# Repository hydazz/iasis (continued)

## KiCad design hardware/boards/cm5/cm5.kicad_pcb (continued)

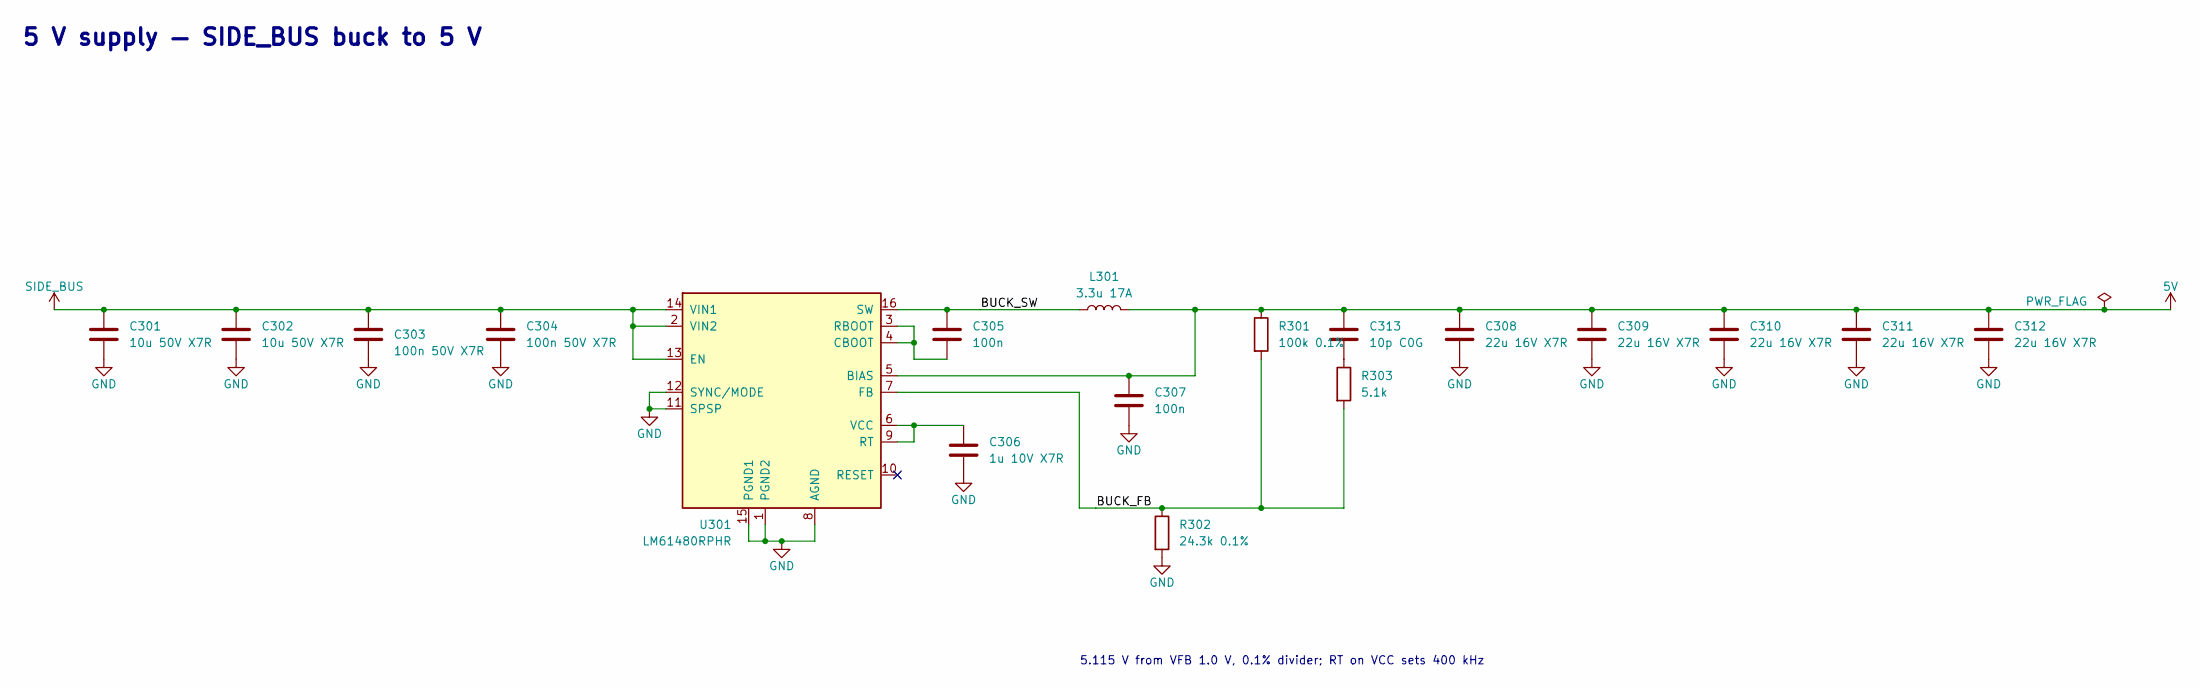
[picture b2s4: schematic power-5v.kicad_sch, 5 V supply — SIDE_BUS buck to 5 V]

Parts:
C301, C302: 10u 50V X7R; C_1210_3225Metric; MPN CL32B106KBJNNNE; LCSC C138687
C303, C304: 100n 50V X7R; C_0402_1005Metric; MPN CL05B104KB54PNC; LCSC C307331
C305, C307: 100n; C_0402_1005Metric; MPN CL05B104KO5NNNC; LCSC C1525
C306: 1u 10V X7R; C_0603_1608Metric; MPN CGA0603X7R105K100JT; LCSC C22399625
C308, C309, C310, C311, C312: 22u 16V X7R; C_1210_3225Metric; MPN CL32B226KOJNNNE; LCSC C55530
C313: 10p C0G; C_0402_1005Metric; MPN CL05C100JB5NNNC; LCSC C32949
L301: 3.3u 17A; L_PROD_PSPMAA0805; MPN PSPMAA0805-3R3M-ANP; LCSC C2962881
R301: 100k 0.1%; R_0402_1005Metric; MPN ARG02BTC1003; LCSC C2984406
R302: 24.3k 0.1%; R_0402_1005Metric; MPN ARG02BTC2432; LCSC C2681592
R303: 5.1k; R_0402_1005Metric; MPN 0402WGF5101TCE; LCSC C25905
U301: LM61480RPHR; TI_RPH0016A; MPN LM61480RPHR; LCSC C3198089

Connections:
5V: C307.1, C308.1, C309.1, C310.1, C311.1, C312.1, C313.1, L301.2, R301.1, U301.5 (BIAS); also elsewhere on the board
/5 V supply/BUCK_FB: R301.2, R302.1, R303.2, U301.7 (FB)
/5 V supply/BUCK_SW: C305.1, L301.1, U301.16 (SW)
GND: C301.2, C302.2, C303.2, C304.2, C306.2, C307.2, C308.2, C309.2, C310.2, C311.2, C312.2, R302.2, U301.1 (PGND2), U301.8 (AGND), U301.11 (SPSP), U301.12 (SYNC/MODE), U301.15 (PGND1); also elsewhere on the board
unnamed: C313.2, R303.1
unnamed: C305.2, U301.3 (RBOOT), U301.4 (CBOOT)
unnamed: C306.1, U301.6 (VCC), U301.9 (RT)
SIDE_BUS: C301.1, C302.1, C303.1, C304.1, U301.2 (VIN2), U301.13 (EN), U301.14 (VIN1); also elsewhere on the board

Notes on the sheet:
5 V supply — SIDE_BUS buck to 5 V
5.115 V from VFB 1.0 V, 0.1% divider; RT on VCC sets 400 kHz

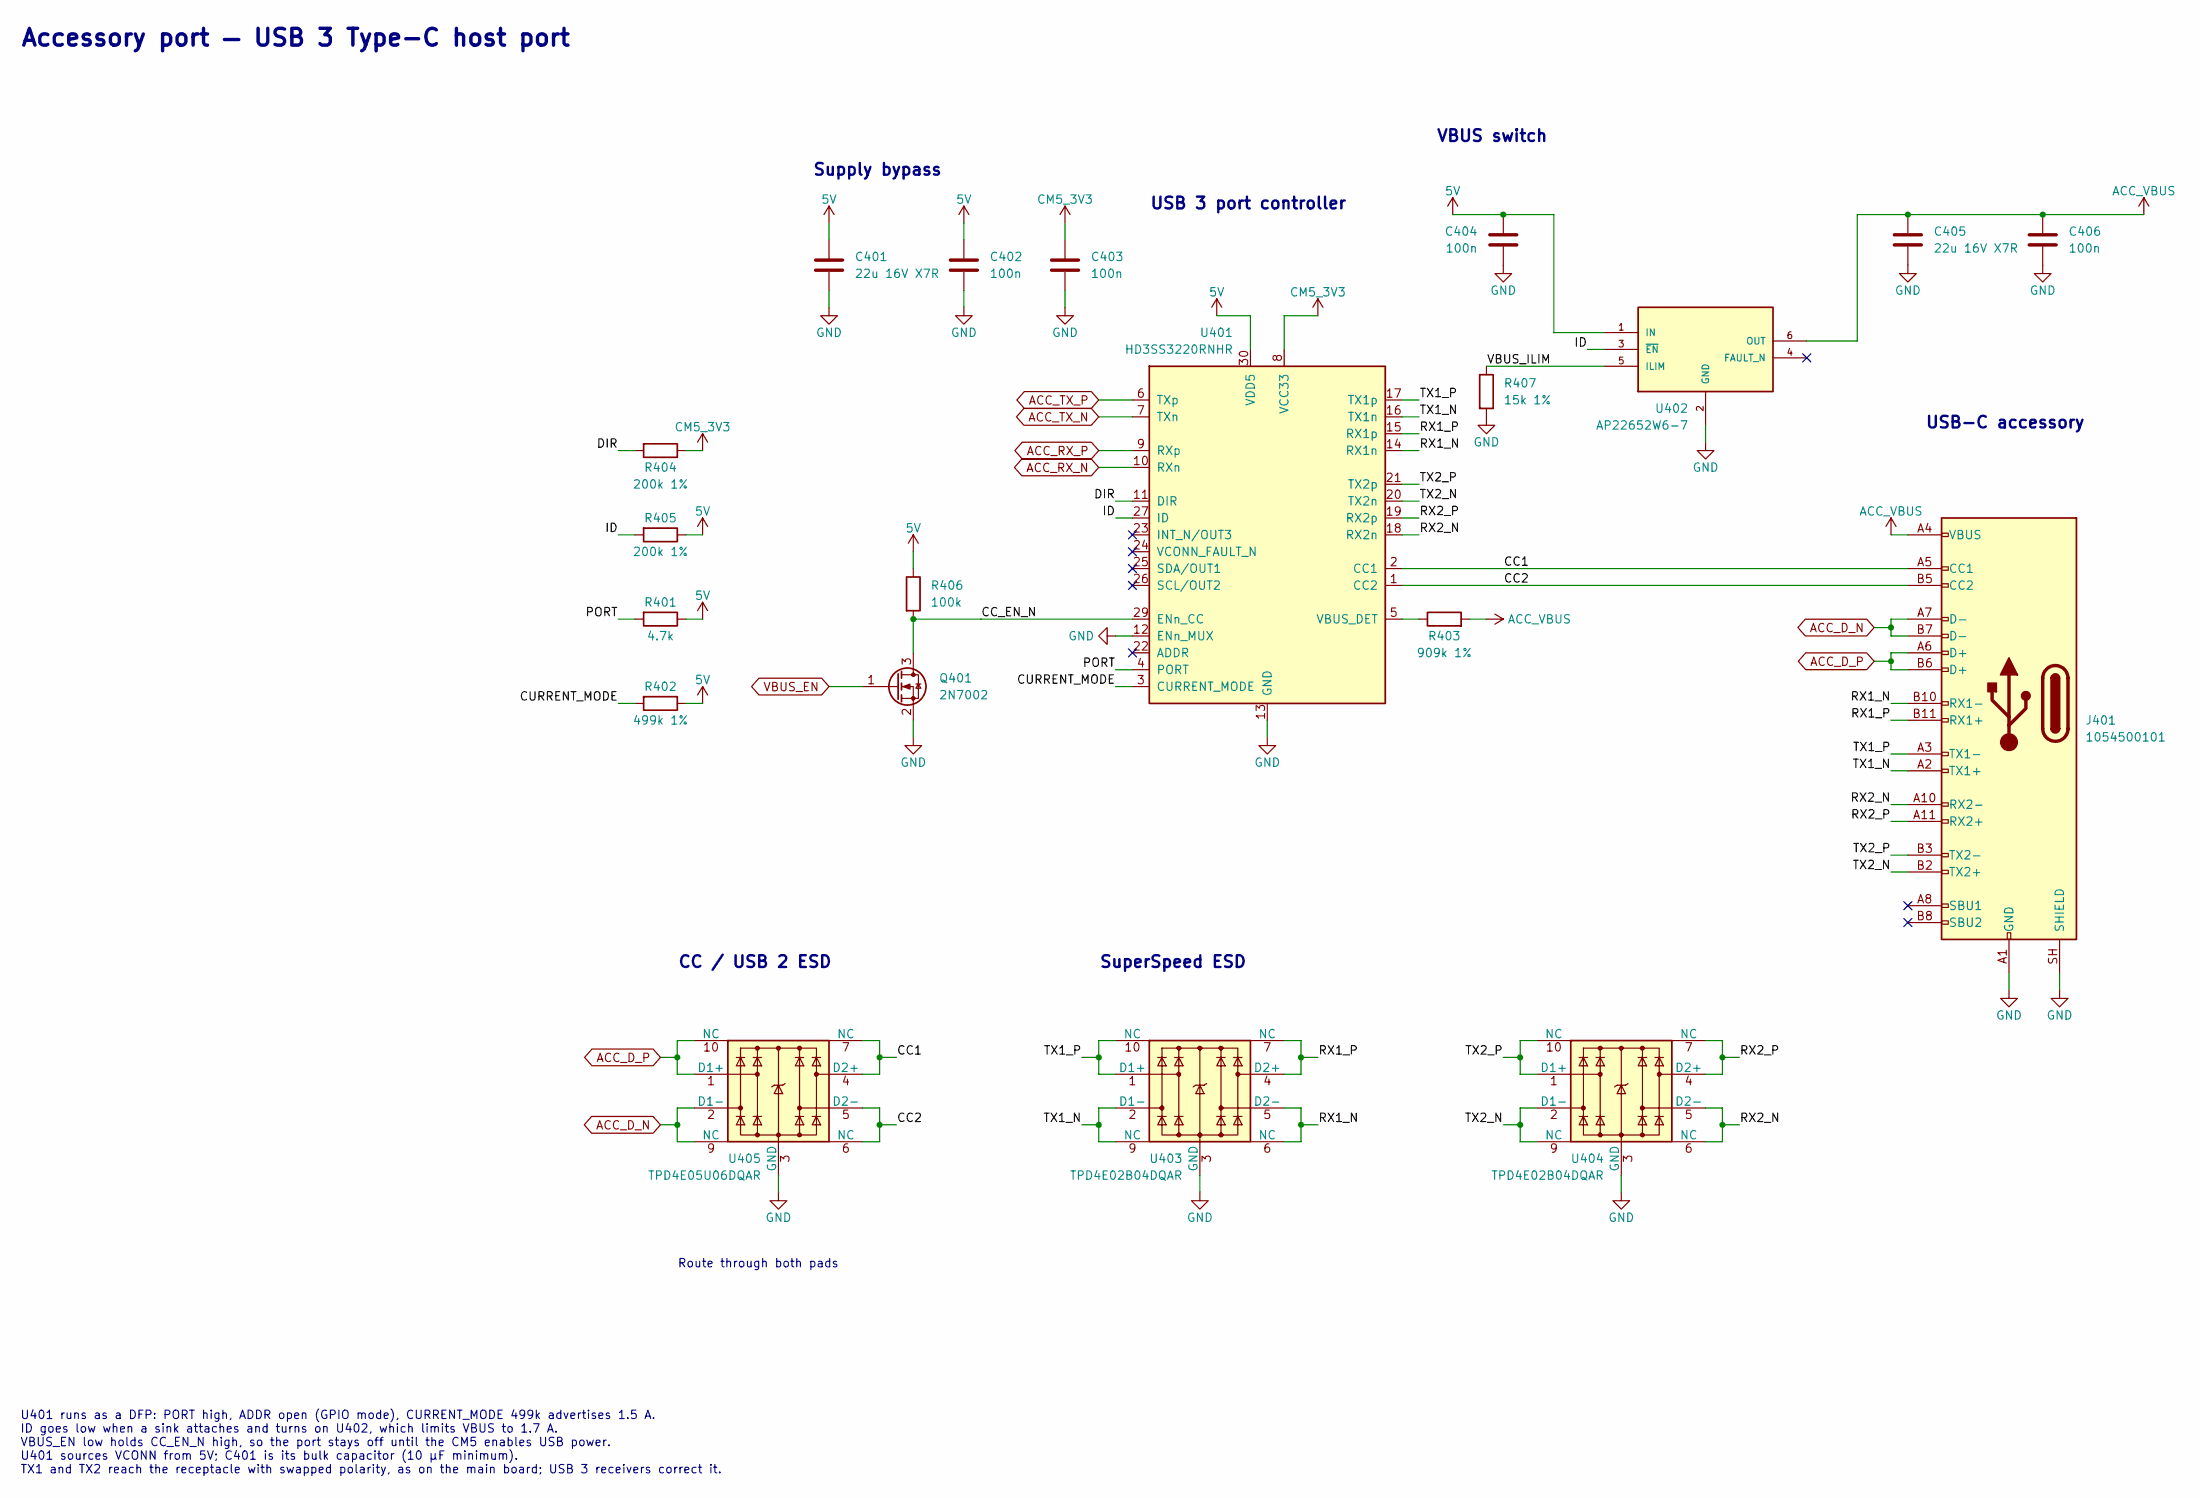
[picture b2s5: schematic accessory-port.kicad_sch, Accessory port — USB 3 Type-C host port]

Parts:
C401, C405: 22u 16V X7R; C_1210_3225Metric; MPN CL32B226KOJNNNE; LCSC C55530
C402, C403, C404, C406: 100n; C_0402_1005Metric; MPN CL05B104KO5NNNC; LCSC C1525
J401: 1054500101; USB_C_Receptacle_Molex_105450-0101; MPN 1054500101; LCSC C134092
Q401: 2N7002; SOT-23; MPN 2N7002; LCSC C8545
R401: 4.7k; R_0402_1005Metric; MPN 0402WGF4701TCE; LCSC C25900
R402: 499k 1%; R_0402_1005Metric; MPN 0402WGF4993TCE; LCSC C25793
R403: 909k 1%; R_0402_1005Metric; MPN 0402WGF9093TCE; LCSC C25799
R404, R405: 200k 1%; R_0402_1005Metric; MPN 0402WGF2003TCE; LCSC C25764
R406: 100k; R_0402_1005Metric; MPN 0402WGF1003TCE; LCSC C25741
R407: 15k 1%; R_0402_1005Metric; MPN 0402WGF1502TCE; LCSC C25756
U401: HD3SS3220RNHR; Texas_RNH0030A_WQFN-30-1EP_2.5x4.5mm_P0.4mm_EP1.2x3.2mm; MPN HD3SS3220RNHR; LCSC C165155
U402: AP22652W6-7; SOT-23-6; MPN AP22652W6-7; LCSC C2158038
U403, U404: TPD4E02B04DQAR; USON-10_2.5x1.0mm_P0.5mm; MPN TPD4E02B04DQAR; LCSC C106794
U405: TPD4E05U06DQAR; USON-10_2.5x1.0mm_P0.5mm; MPN TPD4E05U06DQAR; LCSC C138714

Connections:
5V: C401.1, C402.1, C404.1, R401.1, R402.1, R405.1, R406.1, U401.30 (VDD5), U402.1 (IN); also elsewhere on the board
/Accessory port/CC1: J401.A5 (CC1), U401.2 (CC1), U405.4 (D2+), U405.7 (NC)
/Accessory port/CC2: J401.B5 (CC2), U401.1 (CC2), U405.5 (D2-), U405.6 (NC)
/Accessory port/CC_EN_N: Q401.3 (D), R406.2, U401.29 (ENn_CC)
/Accessory port/CURRENT_MODE: R402.2, U401.3 (CURRENT_MODE)
/Accessory port/DIR: R404.2, U401.11 (DIR)
/Accessory port/ID: R405.2, U401.27 (ID), U402.3 (~EN)
/Accessory port/PORT: R401.2, U401.4 (PORT)
/Accessory port/RX1_N: J401.B10 (RX1-), U401.14 (RX1n), U403.5 (D2-), U403.6 (NC)
/Accessory port/RX1_P: J401.B11 (RX1+), U401.15 (RX1p), U403.4 (D2+), U403.7 (NC)
/Accessory port/RX2_N: J401.A10 (RX2-), U401.18 (RX2n), U404.5 (D2-), U404.6 (NC)
/Accessory port/RX2_P: J401.A11 (RX2+), U401.19 (RX2p), U404.4 (D2+), U404.7 (NC)
/Accessory port/TX1_N: J401.A2 (TX1+), U401.16 (TX1n), U403.2 (D1-), U403.9 (NC)
/Accessory port/TX1_P: J401.A3 (TX1-), U401.17 (TX1p), U403.1 (D1+), U403.10 (NC)
/Accessory port/TX2_N: J401.B2 (TX2+), U401.20 (TX2n), U404.2 (D1-), U404.9 (NC)
/Accessory port/TX2_P: J401.B3 (TX2-), U401.21 (TX2p), U404.1 (D1+), U404.10 (NC)
/Accessory port/VBUS_ILIM: R407.1, U402.5 (ILIM)
ACC_D_N: J401.A7 (D-), J401.B7 (D-), U405.2 (D1-), U405.9 (NC); also elsewhere on the board
ACC_D_P: J401.A6 (D+), J401.B6 (D+), U405.1 (D1+), U405.10 (NC); also elsewhere on the board
ACC_RX_N: U401.10 (RXn); also elsewhere on the board
ACC_RX_P: U401.9 (RXp); also elsewhere on the board
ACC_TX_N: U401.7 (TXn); also elsewhere on the board
ACC_TX_P: U401.6 (TXp); also elsewhere on the board
ACC_VBUS: C405.1, C406.1, J401.A4 (VBUS), J401.A9 (VBUS), J401.B4 (VBUS), J401.B9 (VBUS), R403.2, U402.6 (OUT)
CM5_3V3: C403.1, R404.1, U401.8 (VCC33); also elsewhere on the board
GND: C401.2, C402.2, C403.2, C404.2, C405.2, C406.2, J401.A1 (GND), J401.A12 (GND), J401.B1 (GND), J401.B12 (GND), J401.SH (SHIELD), Q401.2 (S), R407.2, U401.12 (ENn_MUX), U401.13 (GND), U401.28 (GND), U401.31 (GND), U402.2 (GND), U403.3 (GND), U403.8 (GND), U404.3 (GND), U404.8 (GND), U405.3 (GND), U405.8 (GND); also elsewhere on the board
unnamed: R403.1, U401.5 (VBUS_DET)
VBUS_EN: Q401.1 (G); also elsewhere on the board

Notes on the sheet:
Accessory port — USB 3 Type-C host port
Supply bypass
USB 3 port controller
VBUS switch
USB-C accessory
CC / USB 2 ESD
SuperSpeed ESD
Route through both pads
U401 runs as a DFP: PORT high, ADDR open (GPIO mode), CURRENT_MODE 499k advertises 1.5 A. ID goes low when a sink attaches and turns on U402, which limits VBUS to 1.7 A. VBUS_EN low holds CC_EN_N high, so the port stays off until the CM5 enables USB power. U401 sources VCONN from 5V; C401 is its bu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

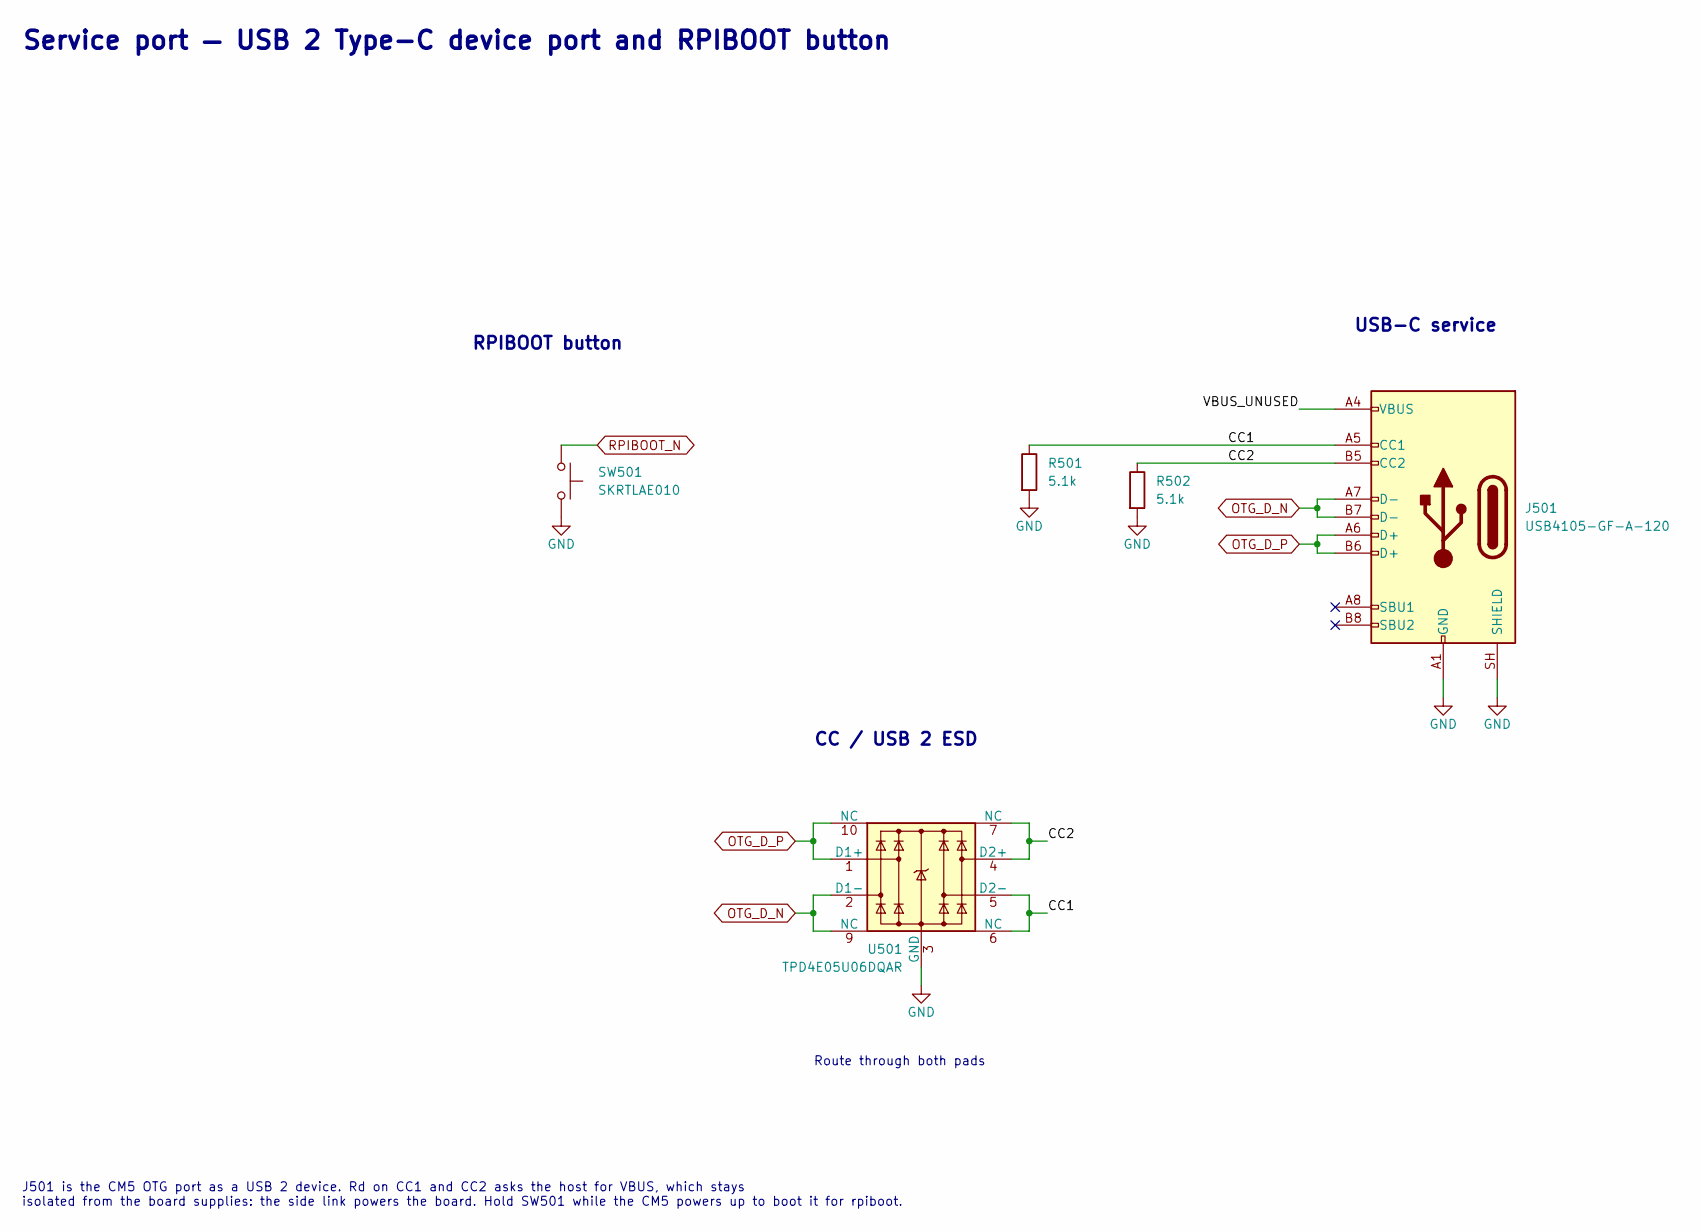
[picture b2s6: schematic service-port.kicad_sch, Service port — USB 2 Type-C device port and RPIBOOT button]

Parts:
J501: USB4105-GF-A-120; GCT_USB4105_GF_A_120; MPN USB4105-GF-A-120; LCSC C5184243
R501, R502: 5.1k; R_0402_1005Metric; MPN 0402WGF5101TCE; LCSC C25905
SW501: SKRTLAE010; SW_Push_1P1T-MP_NO_Horizontal_Alps_SKRTLAE010; MPN SKRTLAE010; LCSC C110293
U501: TPD4E05U06DQAR; USON-10_2.5x1.0mm_P0.5mm; MPN TPD4E05U06DQAR; LCSC C138714

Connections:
/Service port/CC1: J501.A5 (CC1), R501.1, U501.5 (D2-), U501.6 (NC)
/Service port/CC2: J501.B5 (CC2), R502.1, U501.4 (D2+), U501.7 (NC)
/Service port/VBUS_UNUSED: J501.A4 (VBUS), J501.A9 (VBUS), J501.B4 (VBUS), J501.B9 (VBUS)
GND: J501.A1 (GND), J501.A12 (GND), J501.B1 (GND), J501.B12 (GND), J501.SH (SHIELD), R501.2, R502.2, SW501.2, U501.3 (GND), U501.8 (GND); also elsewhere on the board
OTG_D_N: J501.A7 (D-), J501.B7 (D-), U501.2 (D1-), U501.9 (NC); also elsewhere on the board
OTG_D_P: J501.A6 (D+), J501.B6 (D+), U501.1 (D1+), U501.10 (NC); also elsewhere on the board
RPIBOOT_N: SW501.1; also elsewhere on the board

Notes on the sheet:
Route through both pads
USB-C service
CC / USB 2 ESD
RPIBOOT button
J501 is the CM5 OTG port as a USB 2 device. Rd on CC1 and CC2 asks the host for VBUS, which stays isolated from the board supplies: the side link powers the board. Hold SW501 while the CM5 powers up to boot it for rpiboot.
Service port — USB 2 Type-C device port and RPIBOOT button

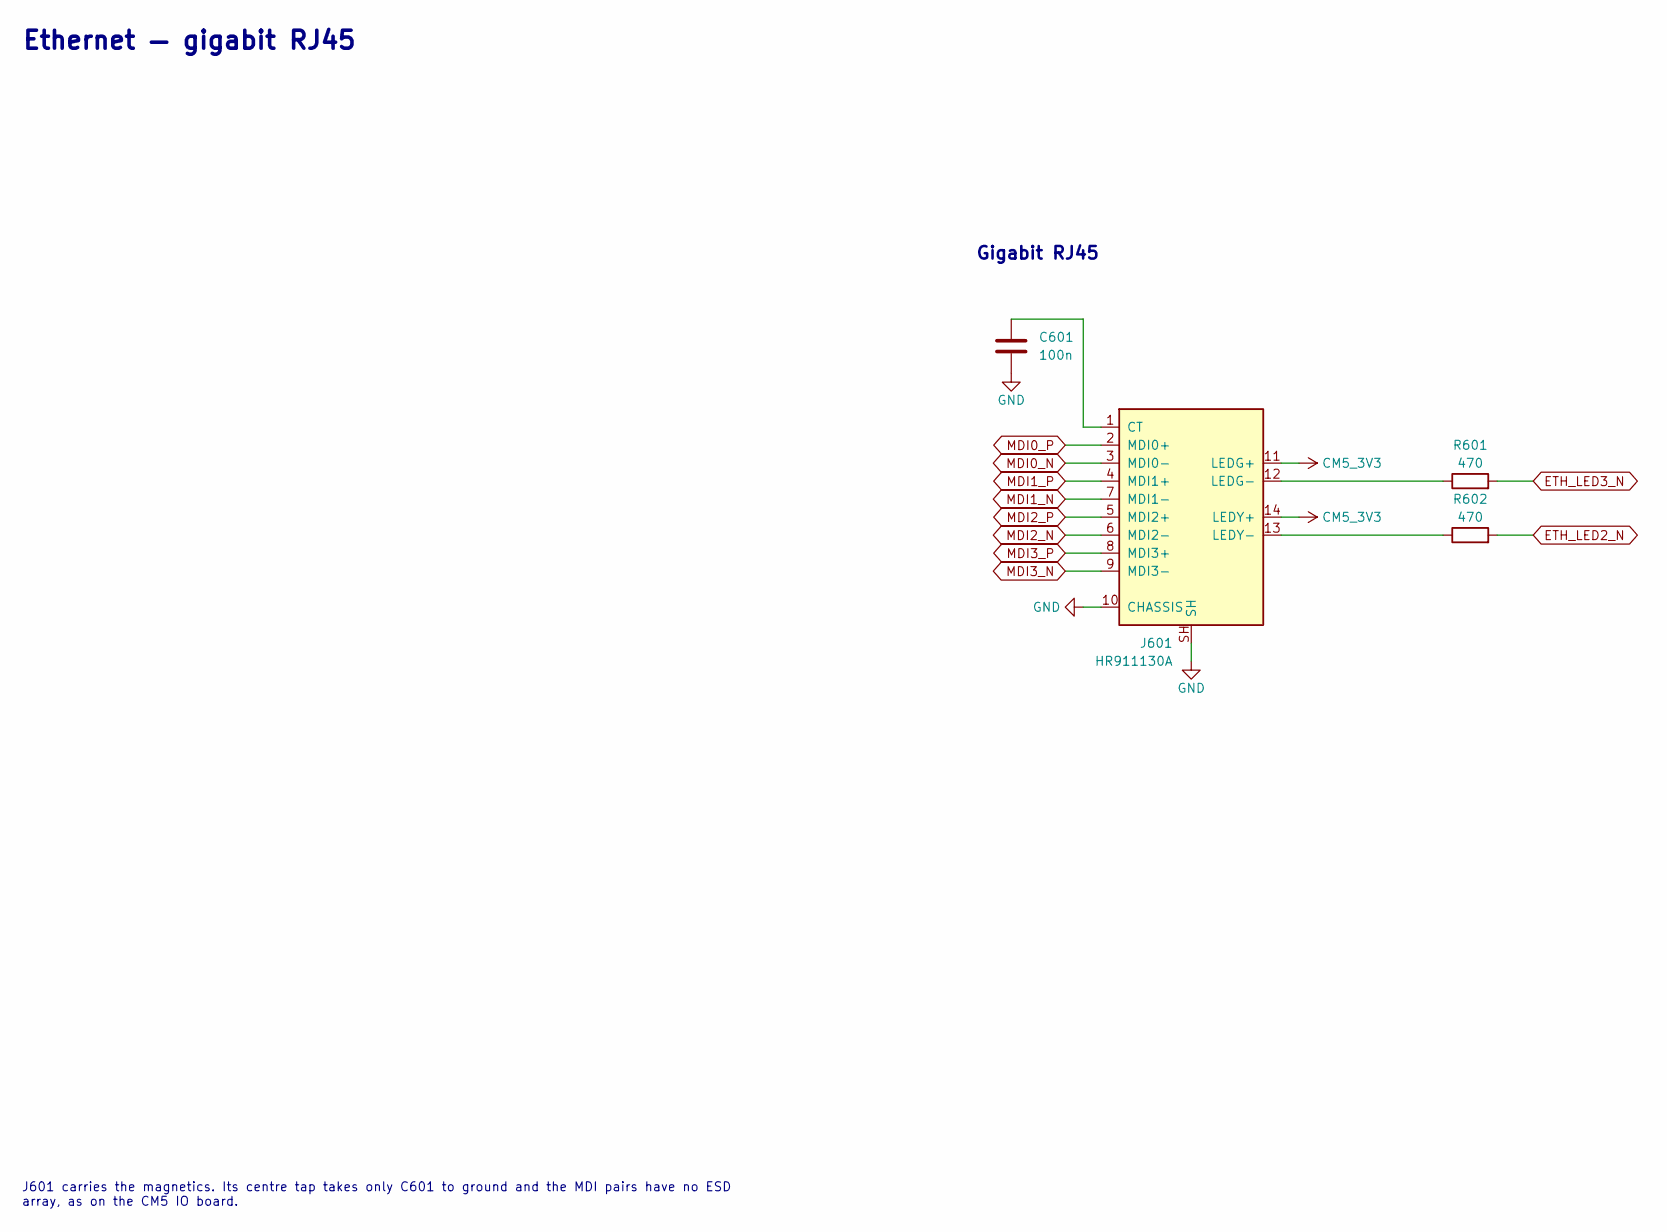
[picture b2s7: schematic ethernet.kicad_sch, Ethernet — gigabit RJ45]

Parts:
C601: 100n; C_0402_1005Metric; MPN CL05B104KO5NNNC; LCSC C1525
J601: HR911130A; HanRun_HR911130A; MPN HR911130A; LCSC C54408
R601, R602: 470; R_0402_1005Metric; MPN 0402WGF4700TCE; LCSC C25117

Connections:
CM5_3V3: J601.11 (LEDG+), J601.14 (LEDY+); also elsewhere on the board
ETH_LED2_N: R602.2; also elsewhere on the board
ETH_LED3_N: R601.2; also elsewhere on the board
GND: C601.2, J601.10 (CHASSIS), J601.SH; also elsewhere on the board
MDI0_N: J601.3 (MDI0-); also elsewhere on the board
MDI0_P: J601.2 (MDI0+); also elsewhere on the board
MDI1_N: J601.7 (MDI1-); also elsewhere on the board
MDI1_P: J601.4 (MDI1+); also elsewhere on the board
MDI2_N: J601.6 (MDI2-); also elsewhere on the board
MDI2_P: J601.5 (MDI2+); also elsewhere on the board
MDI3_N: J601.9 (MDI3-); also elsewhere on the board
MDI3_P: J601.8 (MDI3+); also elsewhere on the board
unnamed: C601.1, J601.1 (CT)
unnamed: J601.12 (LEDG-), R601.1
unnamed: J601.13 (LEDY-), R602.1

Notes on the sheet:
Ethernet — gigabit RJ45
Gigabit RJ45
J601 carries the magnetics. Its centre tap takes only C601 to ground and the MDI pairs have no ESD array, as on the CM5 IO board.

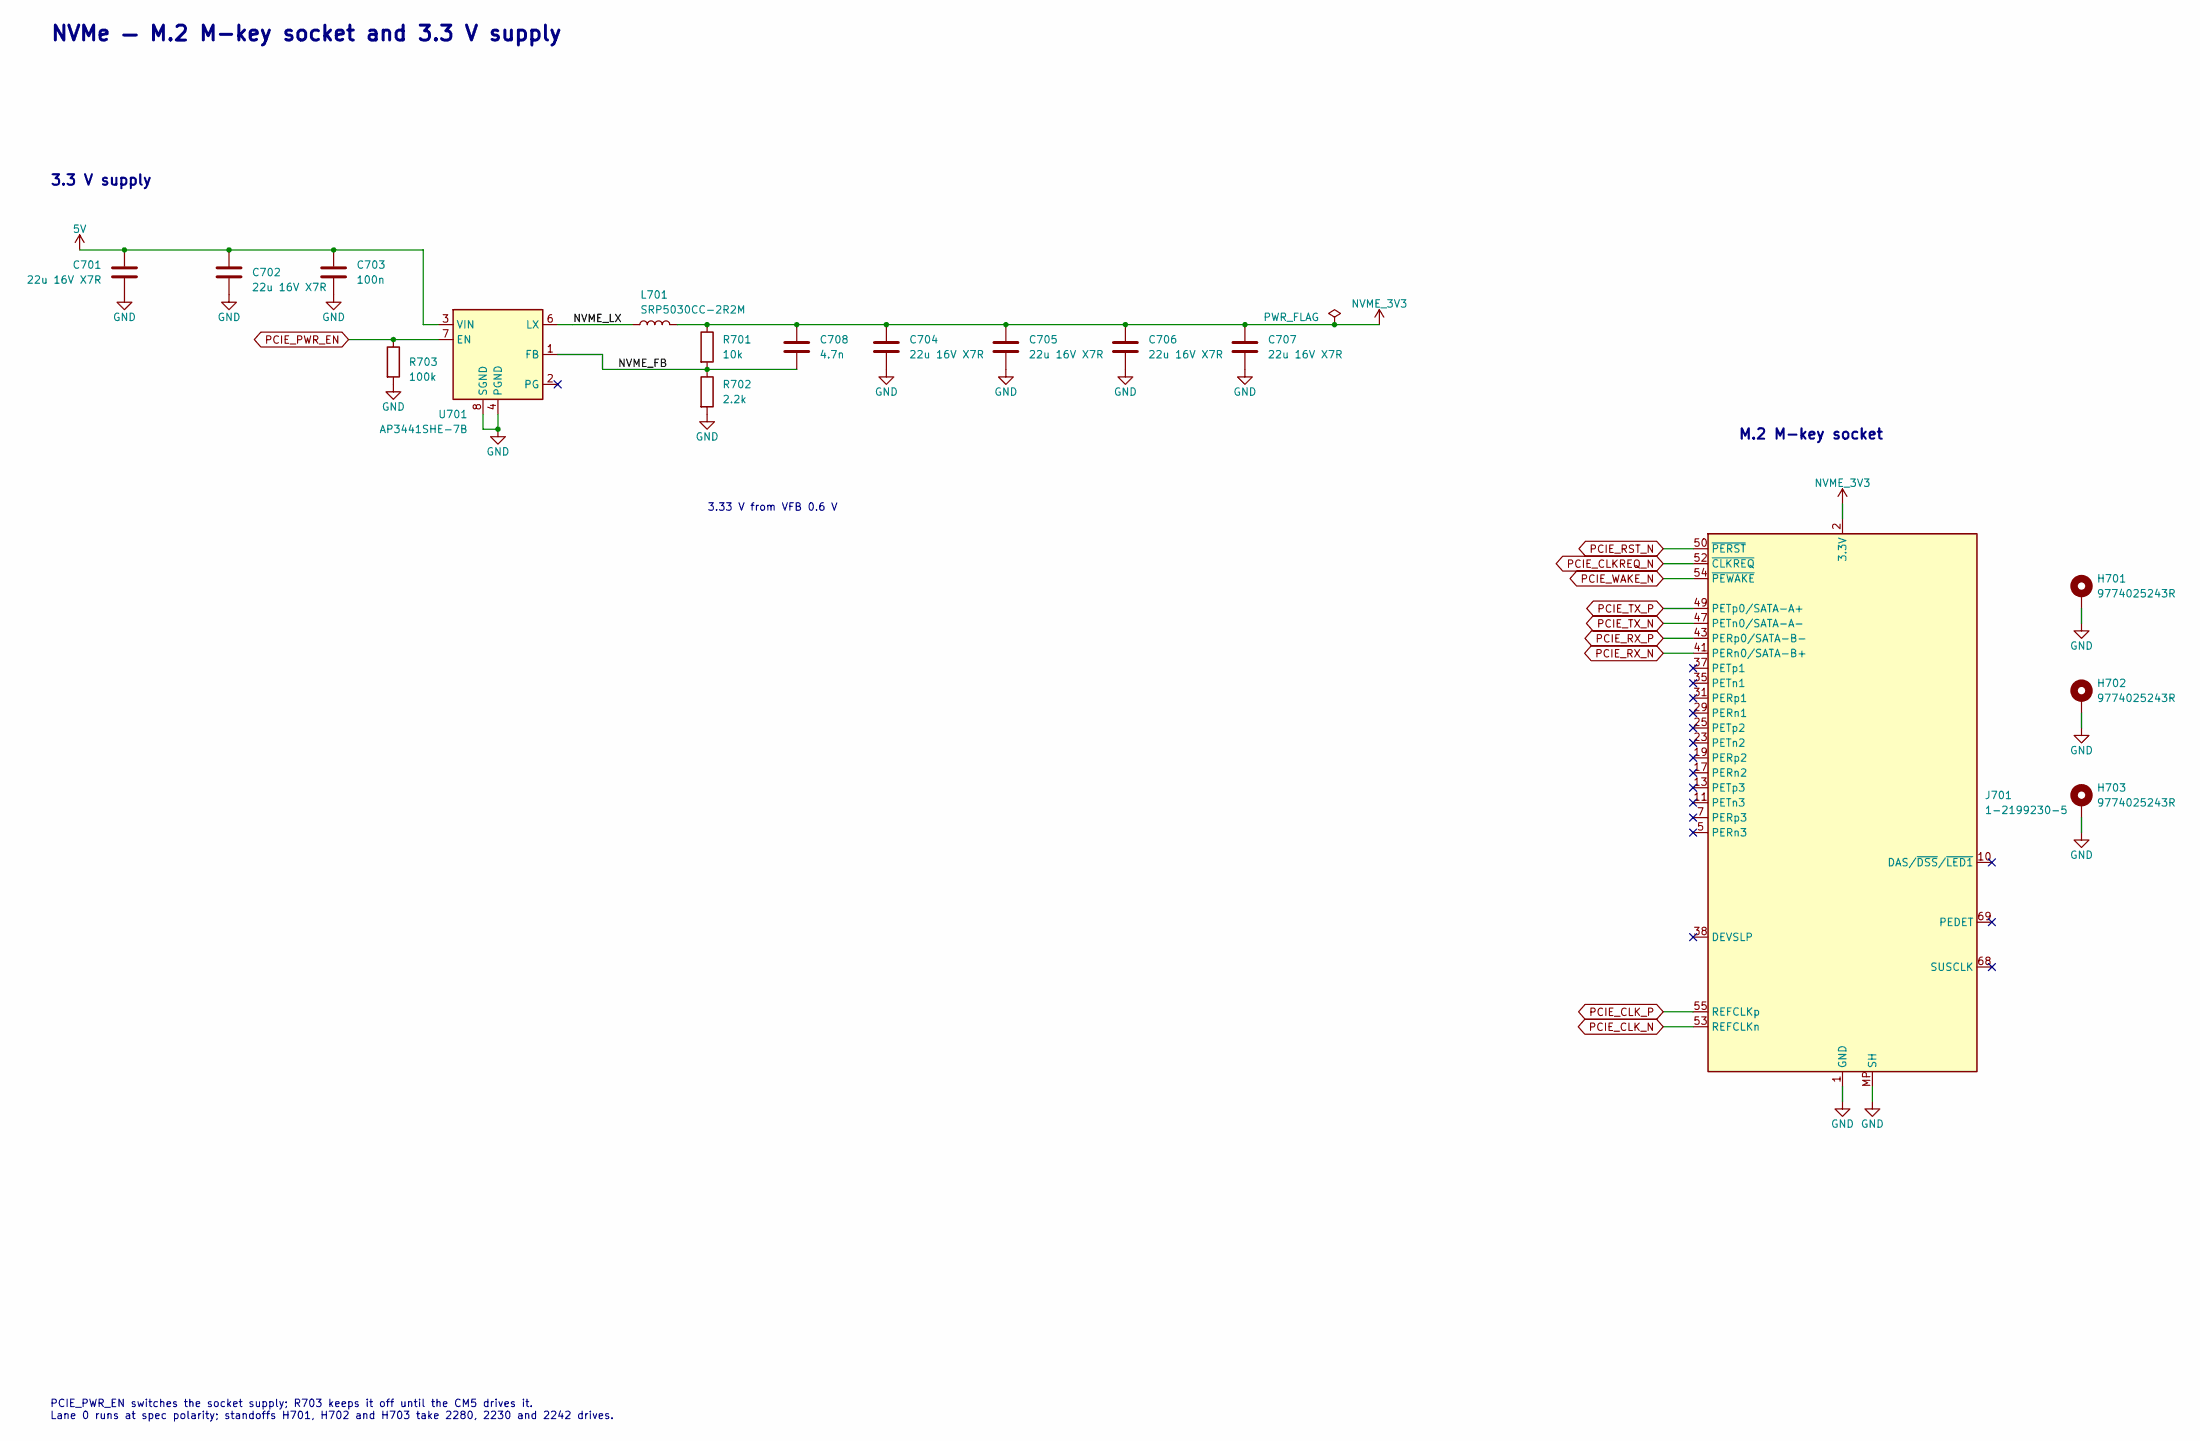
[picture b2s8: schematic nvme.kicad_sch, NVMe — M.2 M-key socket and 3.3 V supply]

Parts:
C701, C702, C704, C705, C706, C707: 22u 16V X7R; C_1210_3225Metric; MPN CL32B226KOJNNNE; LCSC C55530
C703: 100n; C_0402_1005Metric; MPN CL05B104KO5NNNC; LCSC C1525
C708: 4.7n; C_0402_1005Metric; MPN 0402B472K500NT; LCSC C1538
H701, H702, H703: 9774025243R; Mounting_Wuerth_WA-SMSI-M2_H2.5mm_9774025243; MPN 9774025243R; LCSC C22431115
J701: 1-2199230-5; TE_M.2_M_2x38-1MP_P0.5mm; MPN 1-2199230-5; LCSC C590854
L701: SRP5030CC-2R2M; Bourns_SRP5030CC; MPN SRP5030CC-2R2M; LCSC C22404330
R701: 10k; R_0402_1005Metric; MPN 0402WGF1002TCE; LCSC C25744
R702: 2.2k; R_0402_1005Metric; MPN 0402WGF2201TCE; LCSC C25879
R703: 100k; R_0402_1005Metric; MPN 0402WGF1003TCE; LCSC C25741
U701: AP3441SHE-7B; DFN-8-1EP_2x2mm_P0.5mm_EP0.9x1.7mm; MPN AP3441SHE-7B; LCSC C2070918

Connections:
5V: C701.1, C702.1, C703.1, U701.3 (VIN); also elsewhere on the board
/NVMe/NVME_FB: C708.2, R701.2, R702.1, U701.1 (FB)
/NVMe/NVME_LX: L701.1, U701.6 (LX)
GND: C701.2, C702.2, C703.2, C704.2, C705.2, C706.2, C707.2, H701.1 (1_1), H702.1 (1_1), H703.1 (1_1), J701.1 (GND), J701.3 (GND), J701.9 (GND), J701.15 (GND), J701.21 (GND), J701.27 (GND), J701.33 (GND), J701.39 (GND), J701.45 (GND), J701.51 (GND), J701.57 (GND), J701.71 (GND), J701.73 (GND), J701.75 (GND), J701.MP (SH), R702.2, R703.2, U701.4 (PGND), U701.8 (SGND), U701.9 (SGND); also elsewhere on the board
NVME_3V3: C704.1, C705.1, C706.1, C707.1, C708.1, J701.2 (3.3V), J701.4 (3.3V), J701.12 (3.3V), J701.14 (3.3V), J701.16 (3.3V), J701.18 (3.3V), J701.70 (3.3V), J701.72 (3.3V), J701.74 (3.3V), L701.2, R701.1
PCIE_CLKREQ_N: J701.52 (~CLKREQ); also elsewhere on the board
PCIE_CLK_N: J701.53 (REFCLKn); also elsewhere on the board
PCIE_CLK_P: J701.55 (REFCLKp); also elsewhere on the board
PCIE_PWR_EN: R703.1, U701.7 (EN); also elsewhere on the board
PCIE_RST_N: J701.50 (~PERST); also elsewhere on the board
PCIE_RX_N: J701.41 (PERn0/SATA-B+); also elsewhere on the board
PCIE_RX_P: J701.43 (PERp0/SATA-B-); also elsewhere on the board
PCIE_TX_N: J701.47 (PETn0/SATA-A-); also elsewhere on the board
PCIE_TX_P: J701.49 (PETp0/SATA-A+); also elsewhere on the board
PCIE_WAKE_N: J701.54 (~PEWAKE); also elsewhere on the board

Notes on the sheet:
NVMe — M.2 M-key socket and 3.3 V supply
3.3 V supply
M.2 M-key socket
3.33 V from VFB 0.6 V
PCIE_PWR_EN switches the socket supply; R703 keeps it off until the CM5 drives it. Lane 0 runs at spec polarity; standoffs H701, H702 and H703 take 2280, 2230 and 2242 drives.

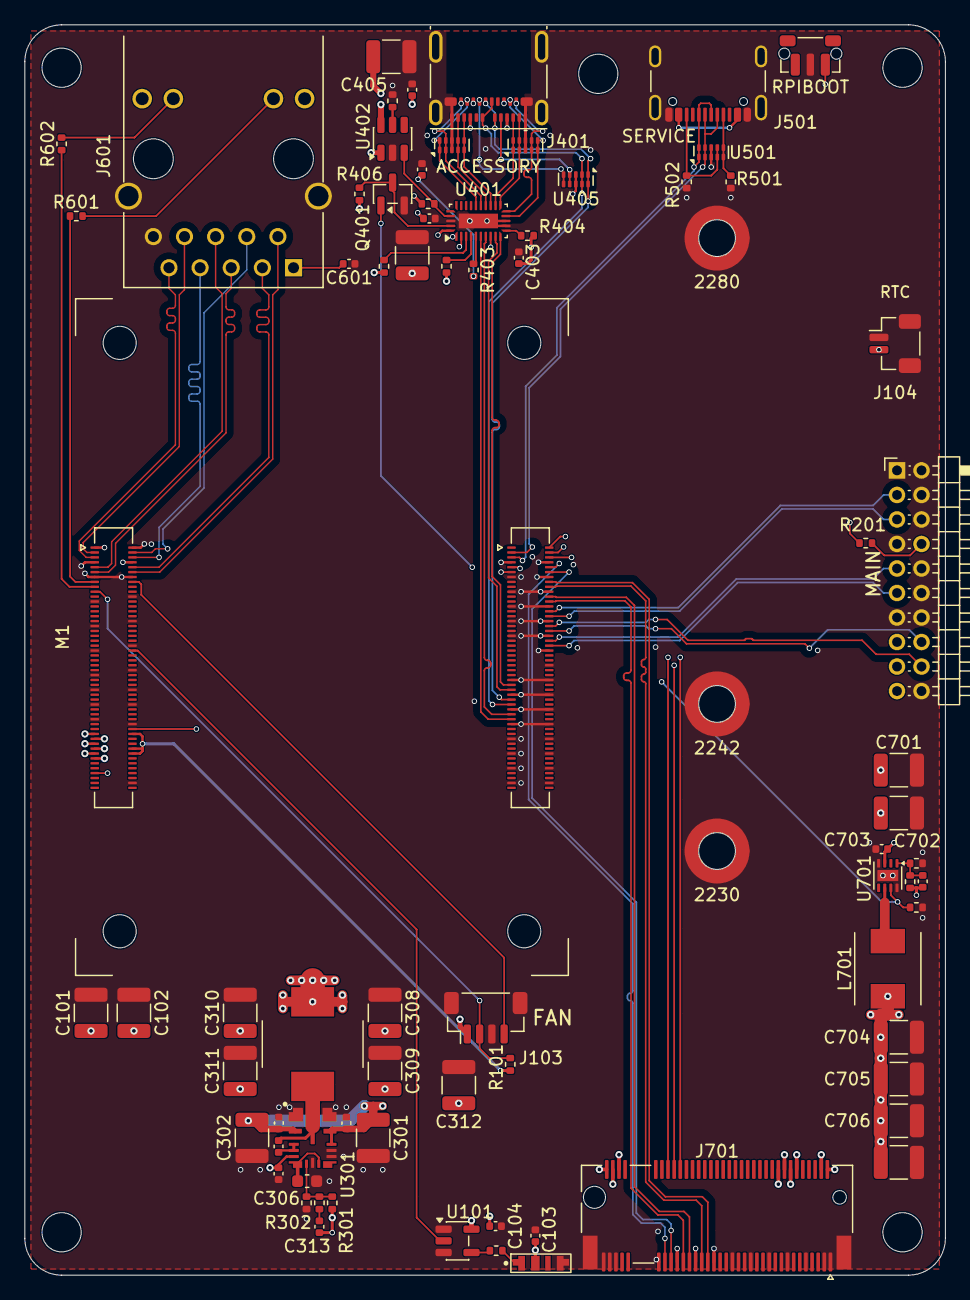
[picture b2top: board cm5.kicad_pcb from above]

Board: 6 copper layers, 75.1 x 102.0 mm, 84 parts (0 on the bottom side), 79 nets.

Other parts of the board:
H1, H2, H3, H4, H5: M3; MountingHole_3.2mm_M3
M1: CM5; RaspberryPi_CM5
